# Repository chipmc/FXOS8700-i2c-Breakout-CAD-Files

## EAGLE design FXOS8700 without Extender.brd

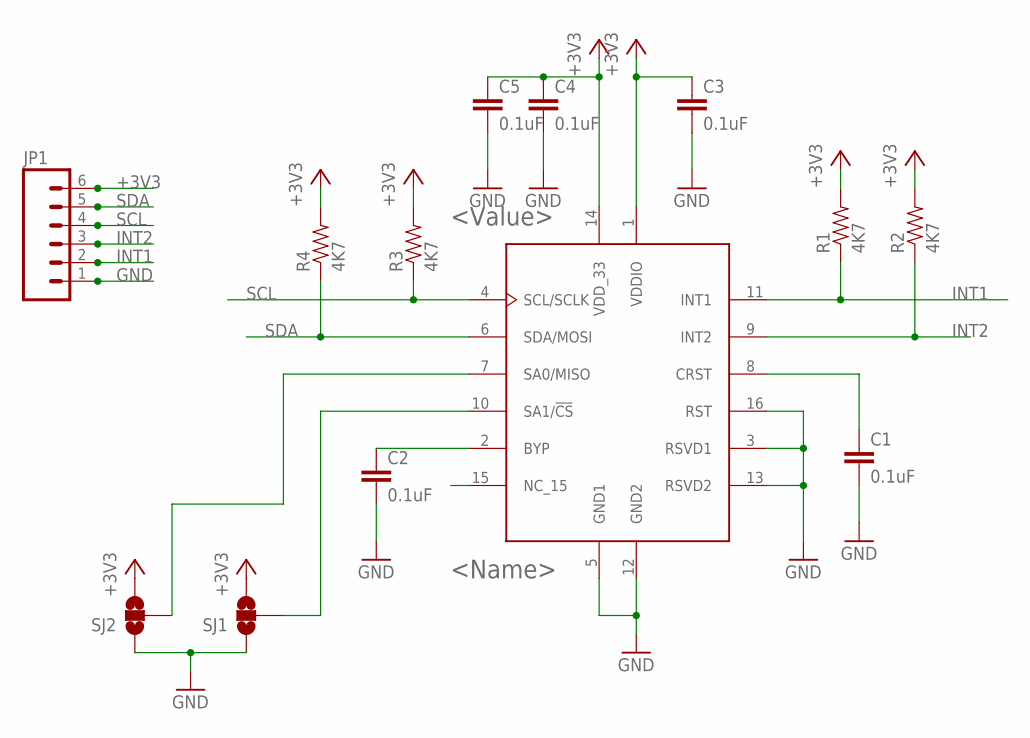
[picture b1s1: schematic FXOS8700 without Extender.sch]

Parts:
C1, C2, C3, C4, C5: 0.1uF; 0805
JP1: M06LOCK; 1X06_LOCK
R1, R2, R3, R4: 4K7; 0805
SJ1, SJ2: SOLDERJUMPER_2WAYPASTE1&2; SJ_3_PASTE1&2
U$1: FXOS870CQ; QFN16_0P5_3X3

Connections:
+3V3: C3.1, C4.1, C5.1, JP1.6, R1.2, R2.2, R3.2, R4.2, SJ1.3, SJ2.3, U$1.1 (VDDIO), U$1.14 (VDD_33)
GND: C1.2, C2.2, C3.2, C4.2, C5.2, JP1.1, SJ1.1, SJ2.1, U$1.3 (RSVD1), U$1.5 (GND1), U$1.12 (GND2), U$1.13 (RSVD2), U$1.16 (RST)
INT1: JP1.2, R1.1, U$1.11 (INT1)
INT2: JP1.3, R2.1, U$1.9 (INT2)
unnamed: C2.1, U$1.2 (BYP)
RST: C1.1, U$1.8 (CRST)
SA0: SJ2.2, U$1.7 (SA0/MISO)
SA1: SJ1.2, U$1.10 (SA1/!CS)
SCL: JP1.4, R3.1, U$1.4 (SCL/SCLK)
SDA: JP1.5, R4.1, U$1.6 (SDA/MOSI)

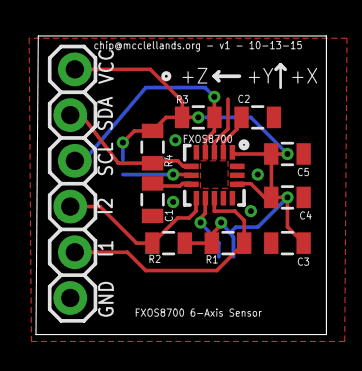
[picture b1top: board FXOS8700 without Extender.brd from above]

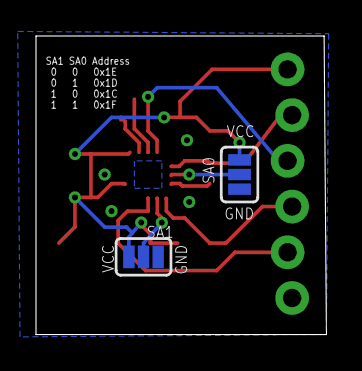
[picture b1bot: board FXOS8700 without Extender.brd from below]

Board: 2 copper layers, 16.1 x 16.6 mm, 13 parts (2 on the bottom side), 10 nets.

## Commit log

2015-10-15 Added EAGLE Files
    Initial load of files

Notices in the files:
parts and their libraries:
SparkFun-Connectors: Licensing: Creative Commons ShareAlike 4.0 International - https://creativecommons.org/licenses/by-sa/4.0
